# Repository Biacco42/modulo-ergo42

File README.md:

# Modulo Ergo42

これは Beta バージョンの組み立てガイドです。Alpha 版は Alpha ブランチのドキュメントを参照してください。

# 組み立てに必要なもの

## Modulo Black Pill Pendant (Black Pill の乗った開発ボード)

- PJ-320d 互換の SMD TRRS **ジャック 2 個** [ex.](https://www.aliexpress.com/item/10Pcs-PJ-320-d-headphone-female-socket-Headphone-socket-Headphone-jack-port-3-1pin-left-three/32771954997.html?spm=a2g0s.9042311.0.0.3da24c4d0cRV8i)
- Black Pill **1 個** [ex.](https://www.aliexpress.com/item/5pcs-STM32F103C8T6-ARM-STM32-Minimum-System-Development-Board-Module-For-arduino/32653839788.html?spm=a2g0s.9042311.0.0.27424c4dzIl8m8)
- SMD 0603 2.2 kΩ **4 個**

## Ergo42 Modulo (両手分)

- 0番1種 m1.4 10 mm 精密ネジ **28 本** [ex.](https://item.rakuten.co.jp/nejiya/400101000014010005_b10/)
- m1.4 ナット **28 個** [ex.](https://item.rakuten.co.jp/nejiya/00n0800010014000005000_b10/)
- PJ-320d 互換の SMD TRRS **ジャック 8 個** [ex.](https://www.aliexpress.com/item/10Pcs-PJ-320-d-headphone-female-socket-Headphone-socket-Headphone-jack-port-3-1pin-left-three/32771954997.html?spm=a2g0s.9042311.0.0.3da24c4d0cRV8i)
- SMD 0603 1 MΩ 抵抗 **4 個**
- SMD 0603 1 uF キャパシタ **4 個**
- SMD 0603 0.1 uF キャパシタ **4 個**
- DPST DIP スイッチ **2 個** [ex.](http://akizukidenshi.com/catalog/g/gP-08928/)
- Kailh MX Socket **56 個** [ex.](https://yushakobo.jp/shop/a01ps/)
- TCA9555 **4 個** [ex.](https://www.digikey.jp/product-detail/ja/texas-instruments/TCA9555PWR/296-24827-1-ND/2094665)

# 組み立て

## Modulo Black Pill Pendant Beta

1. Black Pill 付属のピンをはんだ付け
1. 2.2 kΩ 抵抗を基板の R1 ～ R4 にはんだ付け
1. TRRS ジャックと Black Pill を Pendant の基板にはんだ付け

## Ergo42 Modulo Beta

※フラックス必須です

1. __【注】R1 は実装不要です__
1. R2 / R3 に 1 MΩ 抵抗をはんだ付け
1. C1 / C2 に 0.1 uF を、C3 / C4 に 1 uF をはんだ付け
1. DIP スイッチをはんだ付け (向き不問)
1. TRRS ジャックをはんだ付け  

1. TCA9555 をはんだ付け  
フラックスを基板に塗布してから、マークがついている 1 番ピンが基板上の U1 / U2 シルクの方向を向くように配置してはんだ付けする  

1. Kailh MX Socket をはんだ付け
1. マウントプレートにネジを通してセロハンテープでとめる
1. マウントプレートを裏返して、アクリル片を **2 枚** 重ねてネジに通す  
真ん中の 2 本のネジのところには、角が落とされているアクリル片を通します
1. メイン基板をネジに通す
1. のこりのアクリル片を、**1 枚** ネジに通す
1. ネジ穴がない / ネジ穴が 1 つしかないアクリル片をメイン基板に両面テープ等で固定する
1. 底板をネジに通してナットでとめる
1. 適宜クッションゴム等を貼り付けて完成

# [WIP]ファームウエア

書き込み等開発環境について詳しくは、[KbD Pre](https://biacco42.booth.pm/items/840614) を参照するか、[@Biacco42](https://twitter.com/Biacco42) までお問い合わせください。現在動作するファームウェアは [こちらのリポジトリ](https://github.com/Biacco42/qmk_firmware/tree/feature/modulo-ergo42-proto) の `feature/modulo-ergo42-proto` の `keyboard/modulo/rev2` 配下にあります。

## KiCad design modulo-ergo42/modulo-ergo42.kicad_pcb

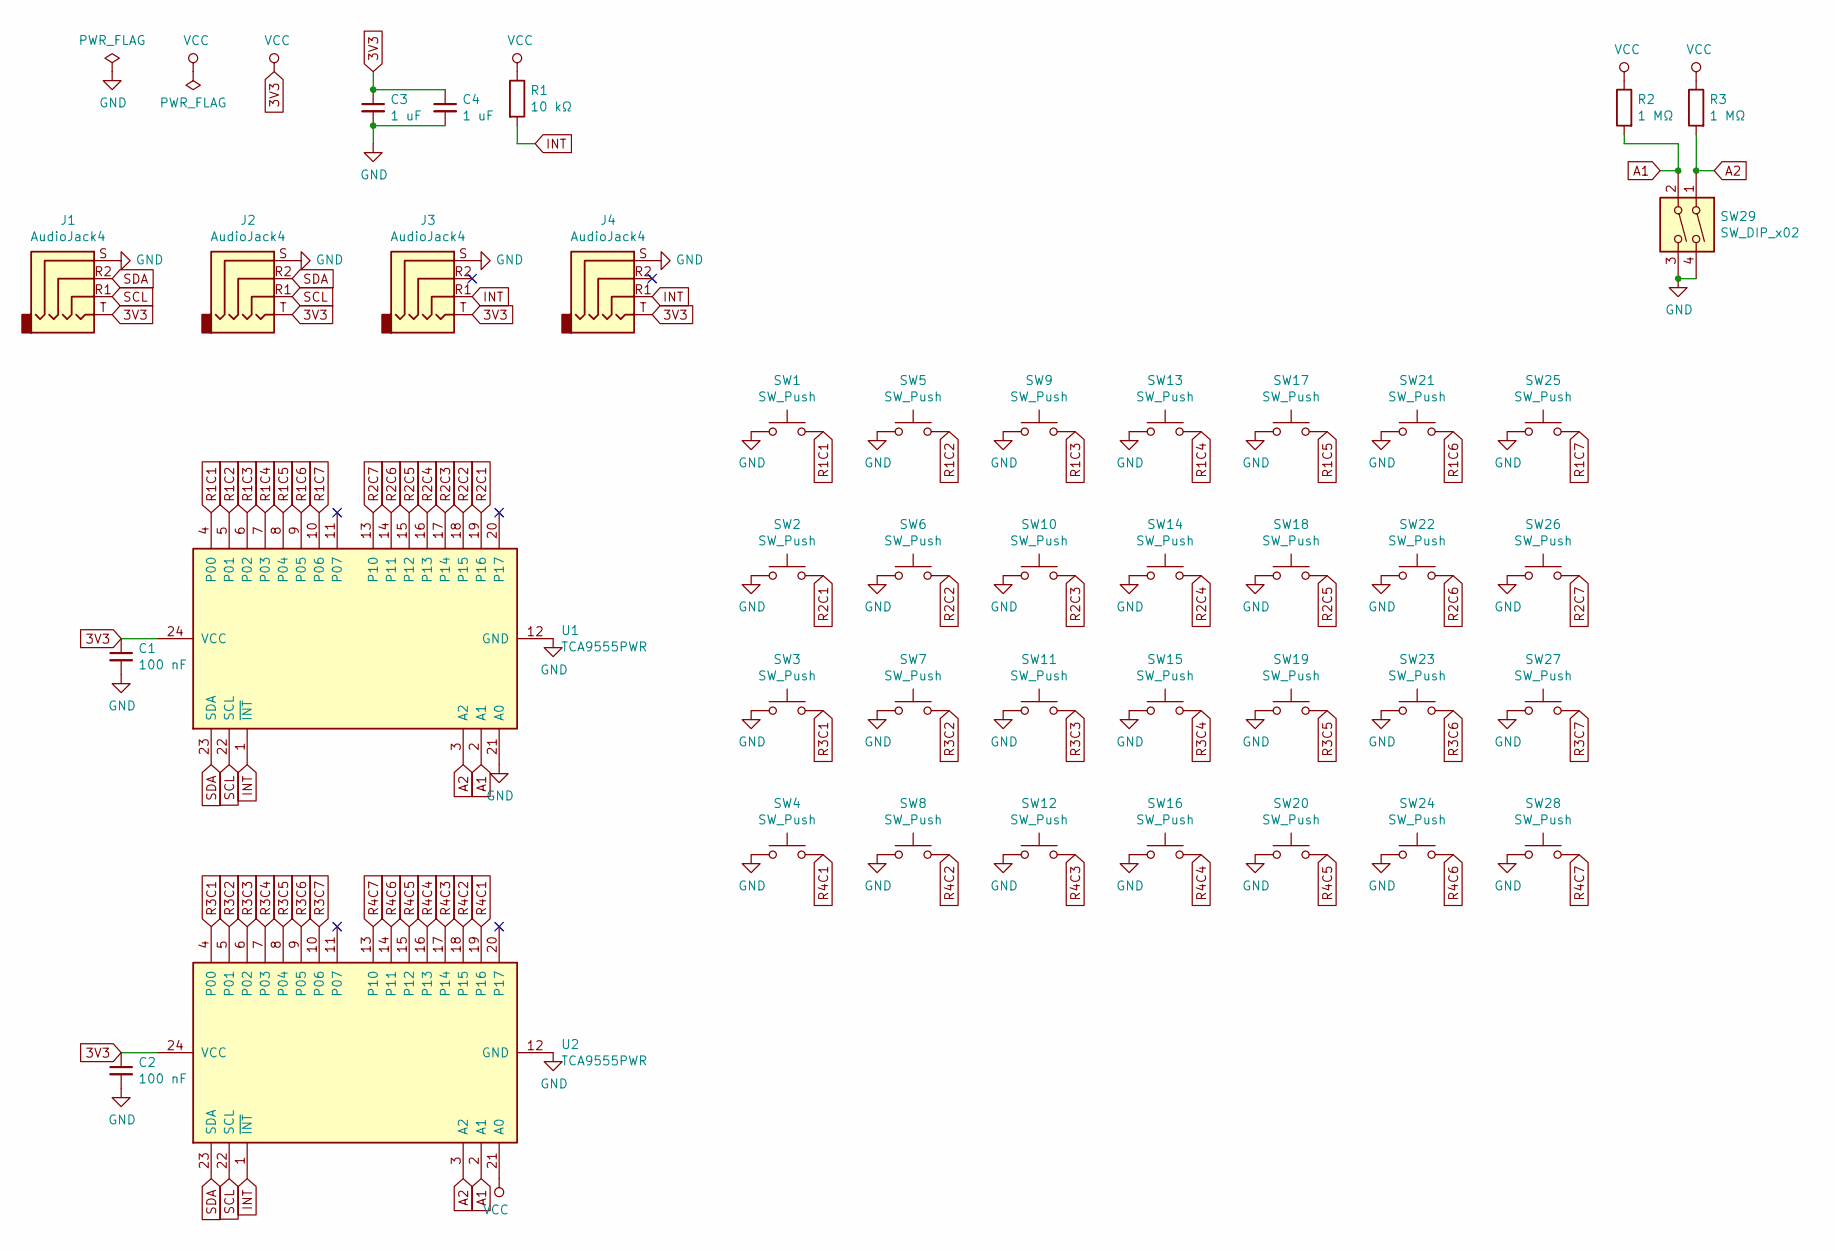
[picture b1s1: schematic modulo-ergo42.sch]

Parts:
C1, C2: 100 nF; C_0603_1608Metric
C3, C4: 1 uF; C_0603_1608Metric
J1, J2, J3, J4: AudioJack4; TRRS_SMD_PJ320
R1: 10 kΩ; R_0603_1608Metric
R2, R3: 1 MΩ; R_0603_1608Metric
SW1, SW2, SW3, SW4, SW5, SW6, SW7, SW8, SW9, SW10, SW11, SW12, SW13, SW14, SW15, SW16, SW17, SW18, SW19, SW20, SW21, SW22, SW23, SW24, SW25, SW26, SW27, SW28: SW_Push; Kailh_Socket
SW29: SW_DIP_x02; DipSwitch
U1, U2: TCA9555PWR; TSSOP-24_4.4x7.8mm_P0.65mm

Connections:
3V3: C1.1, C2.1, C3.1, C4.1, J1.T, J2.T, J3.T, J4.T, R1.1, R2.1, R3.1, U1.24 (VCC), U2.21 (A0), U2.24 (VCC)
A1: R2.2, SW29.2, U1.2 (A1), U2.2 (A1)
A2: R3.2, SW29.1, U1.3 (A2), U2.3 (A2)
GND: C1.2, C2.2, C3.2, C4.2, J1.S, J2.S, J3.S, J4.S, SW1.1, SW2.1, SW3.1, SW4.1, SW5.1, SW6.1, SW7.1, SW8.1, SW9.1, SW10.1, SW11.1, SW12.1, SW13.1, SW14.1, SW15.1, SW16.1, SW17.1, SW18.1, SW19.1, SW20.1, SW21.1, SW22.1, SW23.1, SW24.1, SW25.1, SW26.1, SW27.1, SW28.1, SW29.3, SW29.4, U1.12 (GND), U1.21 (A0), U2.12 (GND)
INT: J3.R1, J4.R1, R1.2, U1.1 (~INT), U2.1 (~INT)
R1C1: SW1.2, U1.4 (P00)
R1C2: SW5.2, U1.5 (P01)
R1C3: SW9.2, U1.6 (P02)
R1C4: SW13.2, U1.7 (P03)
R1C5: SW17.2, U1.8 (P04)
R1C6: SW21.2, U1.9 (P05)
R1C7: SW25.2, U1.10 (P06)
R2C1: SW2.2, U1.19 (P16)
R2C2: SW6.2, U1.18 (P15)
R2C3: SW10.2, U1.17 (P14)
R2C4: SW14.2, U1.16 (P13)
R2C5: SW18.2, U1.15 (P12)
R2C6: SW22.2, U1.14 (P11)
R2C7: SW26.2, U1.13 (P10)
R3C1: SW3.2, U2.4 (P00)
R3C2: SW7.2, U2.5 (P01)
R3C3: SW11.2, U2.6 (P02)
R3C4: SW15.2, U2.7 (P03)
R3C5: SW19.2, U2.8 (P04)
R3C6: SW23.2, U2.9 (P05)
R3C7: SW27.2, U2.10 (P06)
R4C1: SW4.2, U2.19 (P16)
R4C2: SW8.2, U2.18 (P15)
R4C3: SW12.2, U2.17 (P14)
R4C4: SW16.2, U2.16 (P13)
R4C5: SW20.2, U2.15 (P12)
R4C6: SW24.2, U2.14 (P11)
R4C7: SW28.2, U2.13 (P10)
SCL: J1.R1, J2.R1, U1.22 (SCL), U2.22 (SCL)
SDA: J1.R2, J2.R2, U1.23 (SDA), U2.23 (SDA)

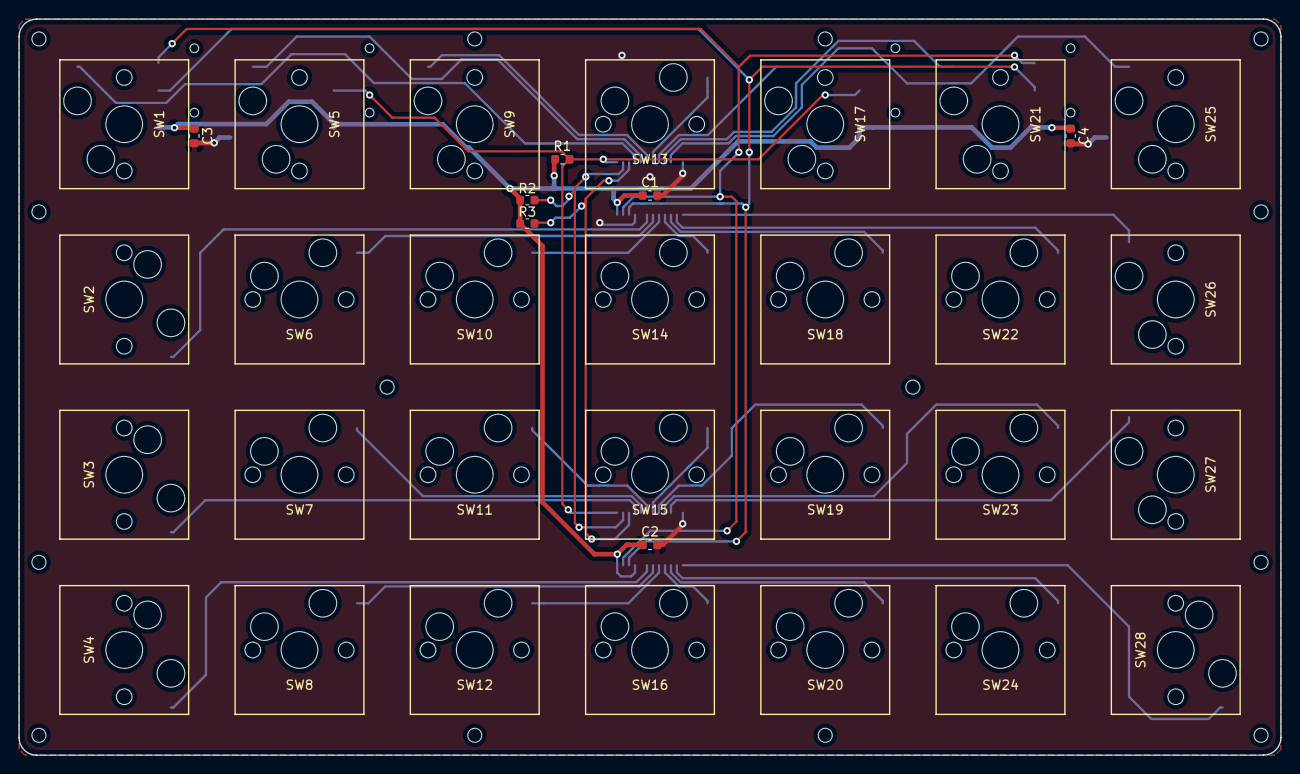
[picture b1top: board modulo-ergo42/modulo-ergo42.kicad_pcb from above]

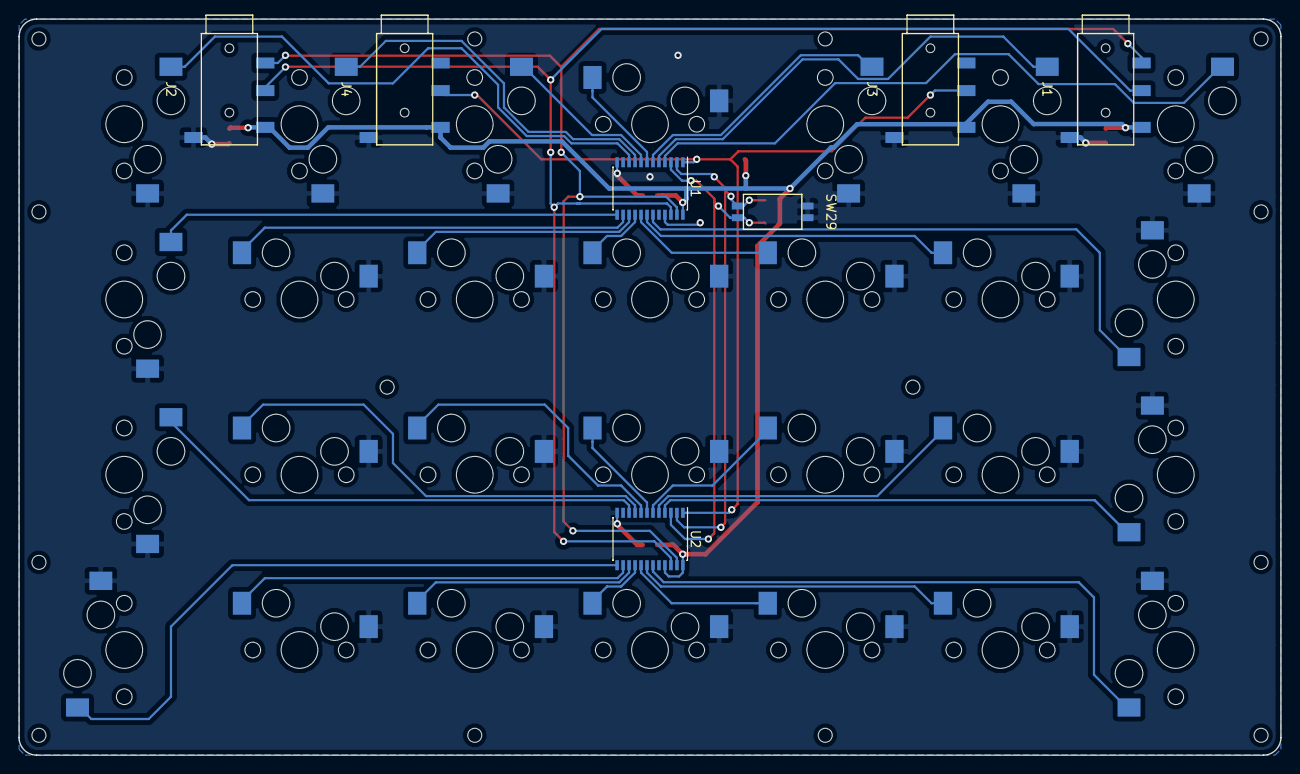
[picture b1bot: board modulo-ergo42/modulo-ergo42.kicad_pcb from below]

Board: 2 copper layers, 137.2 x 80.0 mm, 42 parts (7 on the bottom side), 35 nets.

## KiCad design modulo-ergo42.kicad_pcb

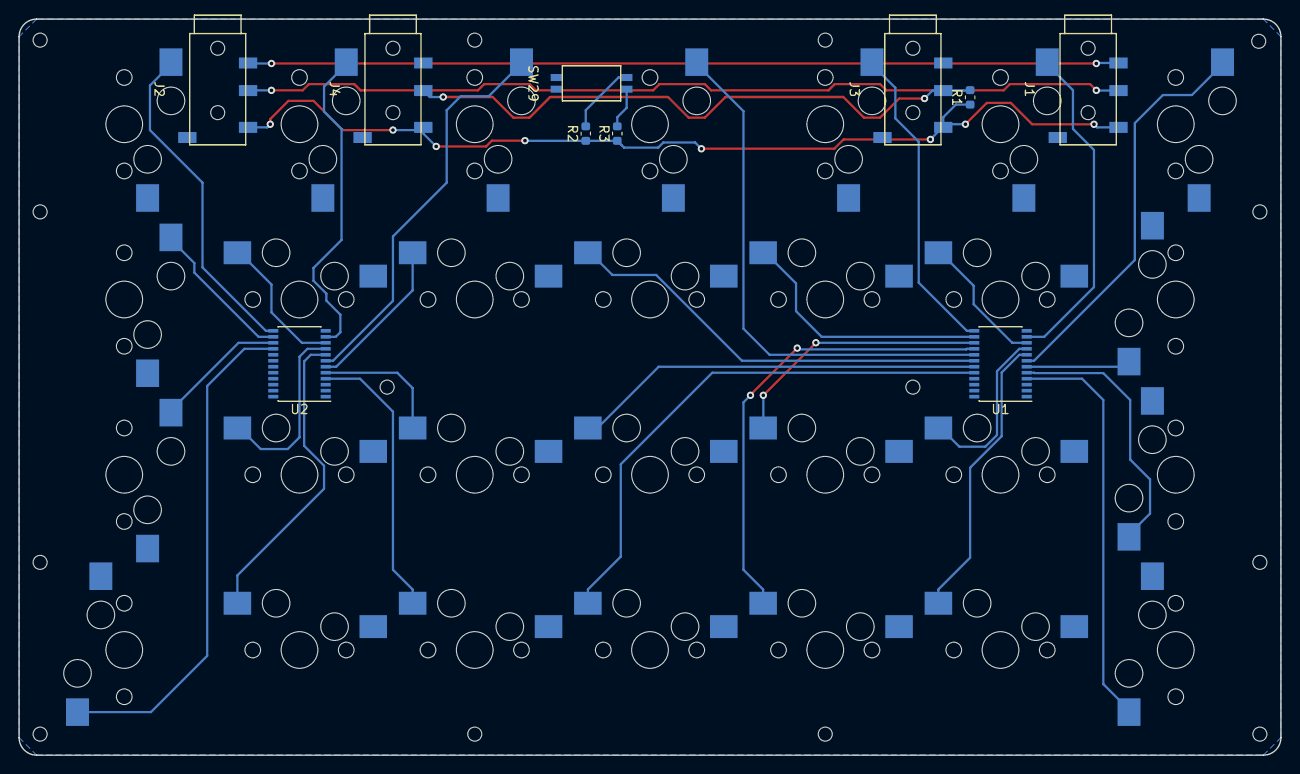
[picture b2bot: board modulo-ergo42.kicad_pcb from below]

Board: 2 copper layers, 137.2 x 80.0 mm, 38 parts (10 on the bottom side), 35 nets.

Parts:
J1, J2, J3, J4: AudioJack4_Ground; TRRS_SMD_PJ320
R1, R2, R3: 10 kΩ; R_0603_1608Metric
SW1, SW2, SW3, SW4, SW5, SW6, SW7, SW8, SW9, SW10, SW11, SW12, SW13, SW14, SW15, SW16, SW17, SW18, SW19, SW20, SW21, SW22, SW23, SW24, SW25, SW26, SW27, SW28: SW_Push; Kailh_Socket
SW29: SW_DIP_x02; DipSwitch
U1, U2: TCA9555PWR; TSSOP-24_4.4x7.8mm_P0.65mm

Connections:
3V3: J1.T, J2.T, J3.T, J4.T, R1.1, R2.1, R3.1, U1.24, U2.21, U2.24
A1: R2.2, SW29.2, U1.2, U2.2
A2: R3.2, SW29.1, U1.3, U2.3
GND: J1.S, J2.S, J3.S, J4.S, SW1.1, SW2.1, SW3.1, SW4.1, SW5.1, SW6.1, SW7.1, SW8.1, SW9.1, SW10.1, SW11.1, SW12.1, SW13.1, SW14.1, SW15.1, SW16.1, SW17.1, SW18.1, SW19.1, SW20.1, SW21.1, SW22.1, SW23.1, SW24.1, SW25.1, SW26.1, SW27.1, SW28.1, SW29.3, SW29.4, U1.12, U1.21, U2.12
INT: J3.R1, J4.R1, R1.2, U1.1, U2.1
R1C1: SW1.2, U1.7
R1C2: SW5.2, U1.11
R1C3: SW9.2, U1.13
R1C4: SW13.2, U1.17
R1C5: SW17.2, U2.7
R1C6: SW21.2, U2.11
R1C7: SW25.2, U2.13
R2C1: SW2.2, U1.6
R2C2: SW6.2, U1.10
R2C3: SW10.2, U1.14
R2C4: SW14.2, U1.18
R2C5: SW18.2, U2.6
R2C6: SW22.2, U2.10
R2C7: SW26.2, U2.14
R3C1: SW3.2, U1.5
R3C2: SW7.2, U1.9
R3C3: SW11.2, U1.15
R3C4: SW15.2, U1.19
R3C5: SW19.2, U2.5
R3C6: SW23.2, U2.9
R3C7: SW27.2, U2.15
R4C1: SW4.2, U1.4
R4C2: SW8.2, U1.8
R4C3: SW12.2, U1.16
R4C4: SW16.2, U1.20
R4C5: SW20.2, U2.4
R4C6: SW24.2, U2.8
R4C7: SW28.2, U2.16
SCL: J1.R2, J2.R2, U1.22, U2.22
SDA: J1.R1, J2.R1, U1.23, U2.23

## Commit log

2018-10-14 Design schematic
2018-10-14 Layout socket
2018-10-14 Add int socket
2018-10-14 Layout socket, TRRS jack and edge
2018-10-14 [WIP] temp layout
2018-10-21 Re-place parts for drill
2018-10-21 Fix schematics
2018-10-21 Finish PCB
2018-10-22 Add directory
2018-10-22 Add mount plate project
2018-10-22 Place MX hole
2018-10-22 Add origin
2018-10-22 Implement mount plate
2018-10-22 Add bottom plate
2018-10-24 Print design data
2018-10-24 Fix screw hole
2018-10-24 Print design
2018-10-24 Fix bottom plate screw hole
2018-10-24 Fix mount plate screw hole
2018-10-25 Fix TRRS jack
2018-10-26 Add slit for bottom plate
2018-10-27 Add DIP switch window
2018-10-28 Plot gerber for production
2018-10-28 Add bottom plate gerber
2018-10-28 Add mount plate gerber
2018-11-05 Add readme image
2018-12-16 Update schematics for beta
2018-12-17 Make pad narrow
2018-12-17 Implement Beta-1
2018-12-17 Update bottom plate for Beta-1
2018-12-17 Plot PDF
2018-12-18 Add F.Cu / B.Cu print
2018-12-18 Fix some label
2018-12-18 Add print silk
2018-12-18 Plot gerber
